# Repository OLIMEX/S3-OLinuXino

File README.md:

# S3-OLinuXino
IP Camera with S3 SOC from Allwinner, PoE 100Mbit, LCD, micro SD, Flash

This board has:
- Allwinner S3 Cortex-A7 running at 1.2Ghz
- 1Gb DDR3 RAM inside S3 SOC up to 1333Mhz
- 100Mb Ethernet interface with PoE option
- NAND/eMMC/SPI Flash on socket
- WiFi / BT module with RTL8723BS 
- Audio In and Out
- UEXT connector
- Configuration EEPROM
- LCD connector for LCD-OLinuXino
- MIPI camera connector
- CSI camera connector
- Dimensions: 60 x 50 mm

# License
- Hardware is with CERN OHL v1.2 license
- Software is with GPLv3 license
- Documentation is with CC BY-SA 4.0 license

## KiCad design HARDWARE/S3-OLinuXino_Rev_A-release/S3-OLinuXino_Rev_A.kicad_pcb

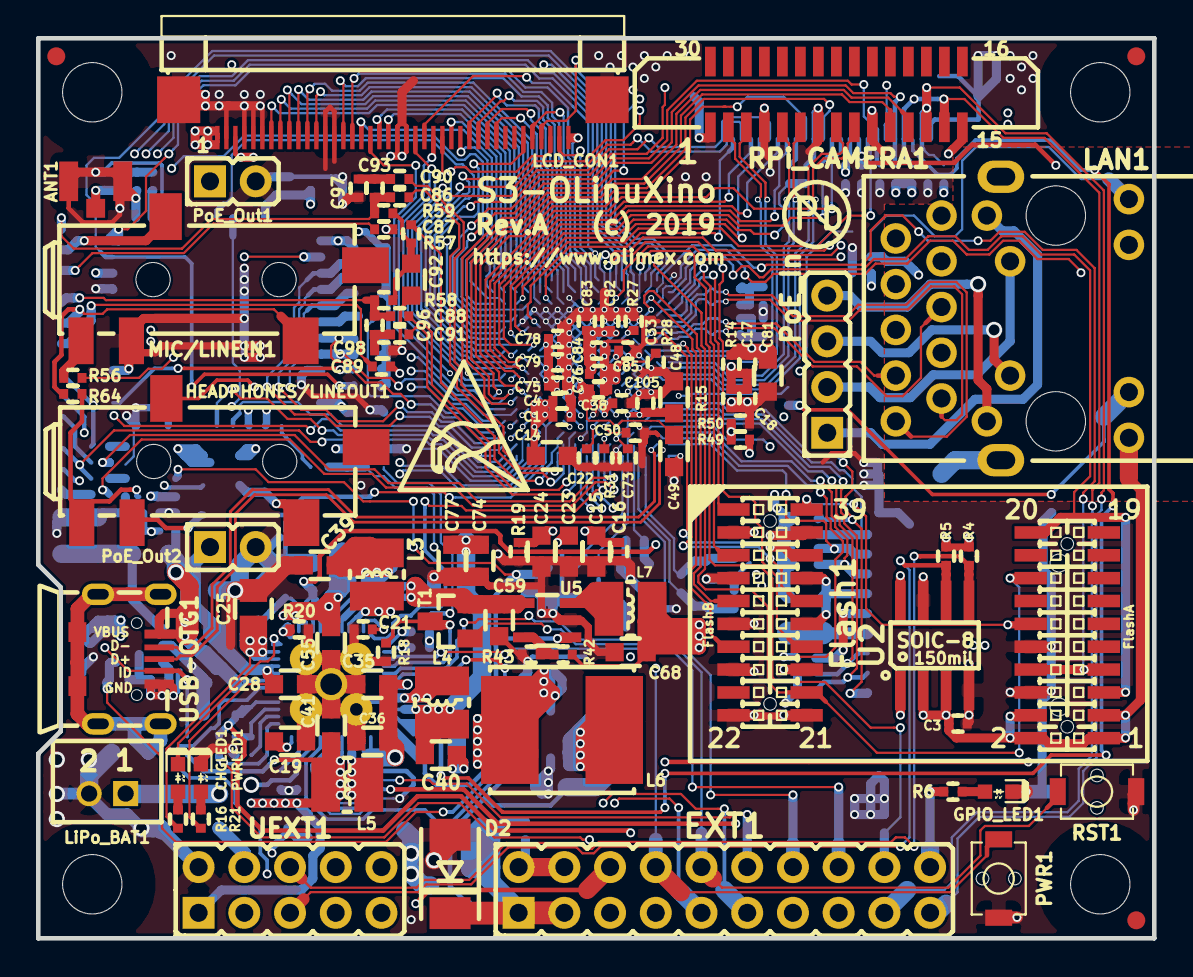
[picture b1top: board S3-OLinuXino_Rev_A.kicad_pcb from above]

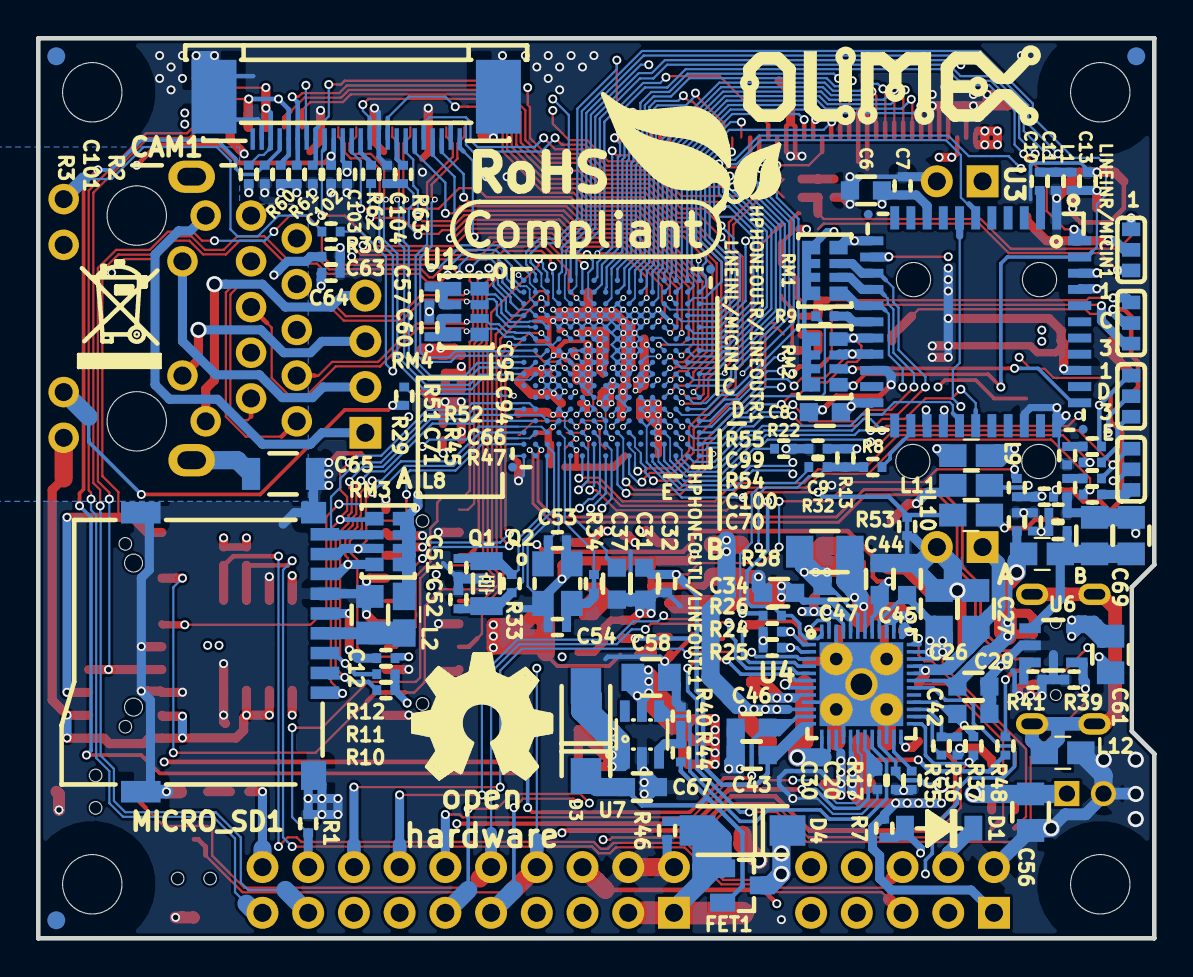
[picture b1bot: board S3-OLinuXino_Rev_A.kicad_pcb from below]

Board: 4 copper layers, 62.0 x 50.0 mm, 233 parts (124 on the bottom side), 224 nets.

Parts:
ANT1: U.FL-R-SMT-1
C1, C3, C4, C7, C9, C16, C17, C18, C20, C22, C33, C38, C57, C60, C63, C64, C66, C71, C73, C75, C76, C78, C79, C82, C83, C84, C85, C86, C87, C88, C89, C90, C91, C94, C95, C99, C100, C101, C102, C103, C105: 100nF/10V/10%/X7R/C0402; C_0402_5MIL_DWS
C6, C8, C14, C15, C29, C31, C34, C35, C36, C39, C40, C41, C55, C59, C67, C68, C74, C77, C81, C92: 10uF/6.3V/20%/X5R/C0603; C_0603_5MIL_DWS
C10: 10pF/50V/5%/COG/C0402; C_0402_5MIL_DWS
C11: 0.8pF/50V/+-0.25pF/COG/C0402; C_0402_5MIL_DWS
C12, C25, C26, C27, C56, C58, C61, C69, C70: 47uF/6.3V/20%/X5R/C0805; C_0805_5MIL_DWS
C13: 1.5pF/50V/+-0.25pF/COG/C0402; C_0402_5MIL_DWS
C19, C47: 2.2uF/6.3V/10%/X5R/C0603; C_0603_5MIL_DWS
C21: 1nF/50V/10%/X7R/C0402; C_0402_5MIL_DWS
C23: NA(10uF/6.3V/20%/X5R/C0603); C_0603_5MIL_DWS
C24, C28, C37, C43, C44, C45, C46, C48, C49: 4.7uF/6.3V/20%/X5R/C0603; C_0603_5MIL_DWS
C30, C32, C50: 100nF/10V/10%/C0402; C_0402_5MIL_DWS
C42: 1uF/10V/20%/X5R/C0603; C_0603_5MIL_DWS
C51, C52: 22pF/50V/5%/COG/C0402; C_0402_5MIL_DWS
C53, C54, C93, C96, C97, C98: 33pF/50V/5%/COG/C0402; C_0402_5MIL_DWS
C65: 1nF/2kV/10%/X7R/C1206; C_1206_5MIL_DWS_ISO
C104: NA(15pF/C0402); C_0402_5MIL_DWS
CAM1: OV2640(FPV-WZB21-24-LF)
CHGLED1: LED/YELLOW/0603; LED_0603_KA
D1: 1N5819(S4SOD-123); SOD-123_1C-2A_KA
D2: SMBJ6.0A; DO214AA_1(K)-2(A)
D3, D4: 1N5822/SS34/SMA; SMA-KA
EXT1: NA(HN2x10); HN2x10
FET1: IRLML6402(SOT-23); SOT23
FID1, FID2, FID3, FID4, FID5, FID6: Fiducial; Fiducial1x3
Flash1: Flash[2x(PA-V16X-2X10-LF)]
GPIO_LED1: LED/Red/0603; LED_0603_KA
HEADPHONES/LINEOUT1: PJ-W47S-05D2-LF; PJ-W47S-05D2-LF_5PIN_V2
HPHONEOUTL/LINEOUTL1: Soldered(1-2);Opened(2-3); SJ_2_SMALL
HPHONEOUTR/LINEOUTR1: Soldered(1-2);Opened(2-3); SJ_2_SMALL
L1: 3.3nH/+-0.1nH/L0402(LQP15MN3N3B02D); L_0402_5MIL_DWS
L2: FB0805/600R/2A; L_0805_5MIL_DWS
L3, L4, L5: 2.2uH/1.5A/72mR/20%/CD32(SPN30302R2MPTE); CD32
L6: 2.2uH/4.5A/28mR/20%/CD75/7.8x7.0x5.0mm(YS75-2R2M); YS75_7X8MM
L7: 2.2uH/1.5A/DCR=72mR/20%/3.00x3.00x1.50mm/CD32(NR3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; CD32
L8, L9, L10, L11, L12: FB0805\600R\2A; L_0805_5MIL_DWS
LAN1: LPJG0926HENL(MagJack_10_100_1000_with_PoE)
LCD_CON1: FPV-WZA21-40-LF
LINEINL/MICIN1: Opened(2-3);Soldered(1-2); SJ_2_SMALL
LINEINR/MICIN1: Opened(2-3);Soldered(1-2); SJ_2_SMALL
LiPo_BAT1: DW02S; LIPO_BAT_VERTICAL_DW02S
Logo-OLimeX_Big: OLIMEX_LOGO_TB
Logo-OSHW: LOGO_OPENHARDWARE_8x8
MH1, MH2, MH3, MH4: Mounting_Hole_NPTH; Mounting_Hole_Drill-3.3mm_Clerance-7mm
MIC/LINEIN1: PJ-W47S-05D2-LF; PJ-W47S-05D2-LF_5PIN_V2
MICRO_SD1: MICRO_SD(TFC-WPAPR-08); TFC-WPAPR-08
PWR1: IT-1185AU2-160G-G-TR; IT1185AU2_V2
PWRLED1: LED\Red\0603; LED_0603_KA
PoE1: [2x(HN1x2)+HN1x4]; PoE[2x(HN1x2)+HN1x4]
Q1: Q32.768kHz/12.5pF/2P/SMD1206; CM7V-T1A(Crystal_Package-1206_3.20x1.50x0.65mm)
Q2: Q24MHZ/20pF/30ppm/4P/3.2x2.5mm; TSX-3.2x2.5mm_GND(3)
R1, R2, R3, R4, R5, R6, R14, R15, R16, R18, R21, R24, R25, R29, R30, R35, R47, R52, R58, R59: 2.2k/R0402; R_0402_5MIL_DWS
R7, R11, R26, R32, R37, R39, R46, R48, R60, R61: 10k/R0402; R_0402_5MIL_DWS
R8, R9, R12, R20, R22, R54, R55, R62, R63: 22R/R0402; R_0402_5MIL_DWS
R10: 100k/R0402; R_0402_5MIL_DWS
R13, R49: NA; R_0402_5MIL_DWS
R17, R19, R51: 200k/1%/R0402; R_0402_5MIL_DWS
R27, R28: 240R/1%/R0402; R_0402_5MIL_DWS
R31: 6.04k/1%/R0402; R_0402_5MIL_DWS
R33: 10M/R0402; R_0402_5MIL_DWS
R34, R53: 0R/R0402(Board_Mounted); R_0402_5MIL_0R(Board_Mounted)
R36: NA(2.2k/R0402); R_0402_5MIL_DWS
R38: 0.03R/1%/R1206; R_1206_5MIL_DWS
R40: 1.1k/1%/R0402; R_0402_5MIL_DWS
R41, R45: 3.9k/1%/R0402; R_0402_5MIL_DWS
R42: 4.99k/1%/R0402; R_0402_5MIL_DWS
R43: 3.32k/1%/R0402; R_0402_5MIL_DWS
R44: 8.25k/1%/R0402; R_0402_5MIL_DWS
R50: 22R; R_0402_5MIL_DWS
R56, R64: NA/R0402; R_0402_5MIL_DWS
R57: 470R/R0402; R_0402_5MIL_DWS
RM1, RM2, RM3: RA1206_(4x0603)_4B8_100k; RA1206_(4X0603)_4B8_xx
RM4: RA1206_(4X0603)_4B8_51R; RA1206_(4X0603)_4B8_xx
RPi_CAMERA1: 1.0mm-pitch_ZIF_SMT-15P; TE_1-1734248-5
RST1: IT-1185AU2-160G-G-TR; IT1185AU2_V2
Sign-Antistatic: LOGO_ANTISTATIC_1
Sign-PbFree: LOGO_PBFREE
Sign-RecycleBin: LOGO_RECYCLEBIN_1
Sign-RoHS: LOGO_ROHS_1
T1: DTA114YKA(SOT-23); SOT23
U1: AllWinner-S3(FBGA-234); FBGA-234(Pitch-0.65mm_Pad-0.3mm_11x11x1.08mm)
U2: AT24C16C-SSHM-T(SOIC-8_150mil); SOIC-8_150mil
U3: RTL8723BS(ComboModule); RL-SM02BD(RTL8723BS)
U4: AXP209(QFN-48); QFN48-6x6mm-OLIMEX_V2
U5: SY8089AAAC(SOT23-5); SOT-23-5
U6: SY6280AAC(SOT23-5); SOT-23-5
U7: MT3608(SOT23-6); SOT23-6
UEXT1: HN2x5
USB-OTG1: MICRO_USB\MISB-SWMM-5B_LF; USB-MICRO_MISB-SWMM-5B_LF

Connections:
+1.1V: C40.2, C49.2, C74.1, C75.1, C76.1, C77.1, C78.1, C79.1, L4.2, U1.G12, U1.H12, U1.J11, U1.J12, U1.K8, U1.K9, U1.K11, U1.L8, U1.M8, U1.N5, U4.10
+1V2: C44.2, C102.2, CAM1.10, U4.41
+2.5V: C30.1, R49.2, U4.19
+2V8: C46.2, C101.2, CAM1.4, U4.11
+3.0VA: C31.2, C32.2, C38.2, C43.2, R51.2, U1.L6, U1.M7, U4.12, U5.1
+3.3V_RTC: C42.2, C50.2, R26.1, R32.1, R37.2, U1.N6, U4.28
+3V3: C1.2, C3.1, C4.2, C6.2, C7.2, C8.2, C9.2, C14.1, C22.1, C41.2, C48.2, C73.1, C103.2, C105.2, CAM1.11, EXT1.7, Flash1.1, Flash1.2, Flash1.3, Flash1.4, L2.1, L5.2, LAN1.15, LAN1.17, LCD_CON1.3, R2.2, R3.2, R4.2, R5.2, R7.2, R10.2, R11.2, R13.2, R24.1, R25.1, R48.2, R60.2, RM1.1.1, RM1.2.1, RM1.3.1, RM1.4.1, RM2.1.1, RM2.2.1, RM2.3.1, RM2.4.1, RM3.1.1, RM3.2.1, RM3.3.1, RM3.4.1, RPi_CAMERA1.15, U1.H11, U1.L11, U1.L12, U1.M4, U1.M5, U1.M11, U1.M12, U1.N7, U1.P5, U1.P12, U2.1, U2.2, U2.3, U2.8, U3.9, U3.22, U4.17, UEXT1.1
+5V: C61.1, D4.1, FET1.3, LCD_CON1.1, U6.5
+5V_EXT: C27.1, C28.1, D2.1, D4.2, EXT1.1, EXT1.3, FET1.1, PoE1.5, PoE1.7, R21.1, R46.2, U4.32, U4.33
+5V_USBOTG: C29.1, C71.1, L8.2, U4.31, USB-OTG1.1
/AP-WAKE-BT: U1.F12, U3.6
/BT-DIS-N: RM2.3.2, U1.C13, U3.34
/BT-PCM-CLK: U1.P14, U3.26
/BT-PCM-DIN: U1.T15, U3.27
/BT-PCM-DOUT: U1.M13, U3.25
/BT-PCM-SYNC: U1.T14, U3.28
/BT-UART-CTS: U1.B8, U3.44
/BT-UART-RX: RM2.4.2, U1.B3, U3.43
/BT-UART-TX: U1.B4, U3.42
/BT-WAKE-AP: U1.N14, U3.7
/CAM-PWDN: CAM1.8, R61.1, U1.D14
/CAM-RST: CAM1.6, R60.1, U1.D15
/CSI-D2: CAM1.24, U1.E12
/CSI-D3: CAM1.23, U1.G15
/CSI-D4: CAM1.19, U1.H13
/CSI-D5: CAM1.21, U1.E13
/CSI-D6: CAM1.22, U1.J13
/CSI-D7: CAM1.20, U1.H14
/CSI-D8: CAM1.18, U1.G14
/CSI-D9: CAM1.16, U1.L13
/CSI-D10: CAM1.14, U1.L16
/CSI-D11: CAM1.12, U1.K13
/CSI-HSYNC: CAM1.9, U1.C14
/CSI-MCLK: R62.2, U1.G13
/CSI-PCLK: C104.1, R63.2, U1.F14
/CSI-VSYNC: CAM1.7, U1.F15
/CTP-INT: LCD_CON1.37, U1.A2
/CTP-RST: LCD_CON1.38, U1.H15
/GPIO_LED: EXT1.20, R6.1, U1.C7
/LCD-PWM: LCD_CON1.36, U1.C8
/LCD_CLK: LCD_CON1.31, U1.A11
/LCD_D2: LCD_CON1.23, U1.K15
/LCD_D3: LCD_CON1.24, U1.C11
/LCD_D4: LCD_CON1.25, U1.J14
/LCD_D5: LCD_CON1.26, U1.J15
/LCD_D6: LCD_CON1.27, U1.B16
/LCD_D7: LCD_CON1.28, U1.C16
/LCD_D10: LCD_CON1.15, U1.B9
/LCD_D11: LCD_CON1.16, U1.A9
/LCD_D12: LCD_CON1.17, U1.C15
/LCD_D13: LCD_CON1.18, U1.L15
/LCD_D14: LCD_CON1.19, U1.A15
/LCD_D15: LCD_CON1.20, U1.B15
/LCD_D18: LCD_CON1.7, U1.B14
/LCD_D19: LCD_CON1.8, U1.A14
/LCD_D20: LCD_CON1.9, U1.B13
/LCD_D21: LCD_CON1.10, U1.A13
/LCD_D22: LCD_CON1.11, U1.B12
/LCD_D23: LCD_CON1.12, U1.C12
/LCD_DE: LCD_CON1.32, U1.B11
/LCD_HSYNC: LCD_CON1.29, U1.C10
/LCD_PWR: LCD_CON1.35, U1.E15
/LCD_VSYNC: LCD_CON1.30, U1.B10
/PB3: EXT1.18, R1.2, U1.C4
/PowerSupply_USB_Audio_Ethernet_Buttons_MiPi-Camera/CHSENSE: C39.2, C47.2, L3.2, R38.2, U4.43
/PowerSupply_USB_Audio_Ethernet_Buttons_MiPi-Camera/CT1: LAN1.11, PoE1.4
/PowerSupply_USB_Audio_Ethernet_Buttons_MiPi-Camera/CT2: LAN1.12, PoE1.3
/PowerSupply_USB_Audio_Ethernet_Buttons_MiPi-Camera/EPHY_LINK_LED: LAN1.16, R29.1
/PowerSupply_USB_Audio_Ethernet_Buttons_MiPi-Camera/EPHY_RX_N: LAN1.6, RM4.4.2, U1.F1
/PowerSupply_USB_Audio_Ethernet_Buttons_MiPi-Camera/EPHY_RX_P: LAN1.3, RM4.3.2, U1.F2
/PowerSupply_USB_Audio_Ethernet_Buttons_MiPi-Camera/EPHY_SPD_LED: LAN1.18, R30.1
/PowerSupply_USB_Audio_Ethernet_Buttons_MiPi-Camera/EPHY_TX_N: LAN1.2, RM4.2.2, U1.E2
/PowerSupply_USB_Audio_Ethernet_Buttons_MiPi-Camera/EPHY_TX_P: LAN1.1, RM4.1.2, U1.E3
/PowerSupply_USB_Audio_Ethernet_Buttons_MiPi-Camera/EXTEN: U4.20, U7.4
/PowerSupply_USB_Audio_Ethernet_Buttons_MiPi-Camera/HPOUTFB: L10.1, R53.2, U1.N11, U1.N12
/PowerSupply_USB_Audio_Ethernet_Buttons_MiPi-Camera/HPOUTL: HPHONEOUTL/LINEOUTL1.1, R54.2, U1.P13
/PowerSupply_USB_Audio_Ethernet_Buttons_MiPi-Camera/HPOUTR: HPHONEOUTR/LINEOUTR1.1, R55.2, U1.N13
/PowerSupply_USB_Audio_Ethernet_Buttons_MiPi-Camera/LINEINL: C89.2, U1.R12
/PowerSupply_USB_Audio_Ethernet_Buttons_MiPi-Camera/LINEINR: C87.2, U1.T12
/PowerSupply_USB_Audio_Ethernet_Buttons_MiPi-Camera/LINEOUTL: C100.1, U1.R6
/PowerSupply_USB_Audio_Ethernet_Buttons_MiPi-Camera/LINEOUTR: C99.1, U1.T6
/PowerSupply_USB_Audio_Ethernet_Buttons_MiPi-Camera/MBIAS: R57.2, U1.P10
/PowerSupply_USB_Audio_Ethernet_Buttons_MiPi-Camera/MCSI_CK+: RPi_CAMERA1.9, U1.J2
/PowerSupply_USB_Audio_Ethernet_Buttons_MiPi-Camera/MCSI_CK-: RPi_CAMERA1.8, U1.J1
/PowerSupply_USB_Audio_Ethernet_Buttons_MiPi-Camera/MCSI_DATA0+: RPi_CAMERA1.3, U1.G3
/PowerSupply_USB_Audio_Ethernet_Buttons_MiPi-Camera/MCSI_DATA0-: RPi_CAMERA1.2, U1.G2
/PowerSupply_USB_Audio_Ethernet_Buttons_MiPi-Camera/MCSI_DATA1+: RPi_CAMERA1.6, U1.H2
/PowerSupply_USB_Audio_Ethernet_Buttons_MiPi-Camera/MCSI_DATA1-: RPi_CAMERA1.5, U1.H1
/PowerSupply_USB_Audio_Ethernet_Buttons_MiPi-Camera/MICIN1_N: C90.2, U1.R10
/PowerSupply_USB_Audio_Ethernet_Buttons_MiPi-Camera/MICIN1_P: C86.2, U1.T10
/PowerSupply_USB_Audio_Ethernet_Buttons_MiPi-Camera/MICIN3_N: C91.2, U1.R9
/PowerSupply_USB_Audio_Ethernet_Buttons_MiPi-Camera/MICIN3_P: C88.2, U1.P9
/PowerSupply_USB_Audio_Ethernet_Buttons_MiPi-Camera/NMI: R26.2, U1.R7, U4.48
/PowerSupply_USB_Audio_Ethernet_Buttons_MiPi-Camera/RESETn: R37.1, U1.P7, U4.25
/PowerSupply_USB_Audio_Ethernet_Buttons_MiPi-Camera/SP1: LAN1.13, PoE1.2
/PowerSupply_USB_Audio_Ethernet_Buttons_MiPi-Camera/SP2: LAN1.14, PoE1.1
/PowerSupply_USB_Audio_Ethernet_Buttons_MiPi-Camera/USB-DRV: R39.2, U4.6, U6.4
/PowerSupply_USB_Audio_Ethernet_Buttons_MiPi-Camera/USB-D_N: U1.R2, USB-OTG1.2
/PowerSupply_USB_Audio_Ethernet_Buttons_MiPi-Camera/USB-D_P: U1.T2, USB-OTG1.3
/PowerSupply_USB_Audio_Ethernet_Buttons_MiPi-Camera/VINT: R35.1, U4.26
/SDC0-CLK: R12.2, U1.P2
/SDC0-CMD: MICRO_SD1.3, R11.1, U1.N2
/SDC0-D0: MICRO_SD1.7, RM3.1.2, U1.P1
/SDC0-D1: MICRO_SD1.8, RM3.2.2, U1.R1
/SDC0-D2: MICRO_SD1.1, RM3.4.2, U1.M2
/SDC0-D3: MICRO_SD1.2, R10.1, U1.N3
/SDC0-DET#: MICRO_SD1.9, RM3.3.2, U1.M1
/SDC2-CLK\SPI0-MISO: Flash1.16, Flash1.23, U1.A3
/SDC2-CMD\SPI0-CLK: Flash1.7, Flash1.8, U1.B2
/SDC2-D0\SPI0-MOSI: Flash1.12, Flash1.39, U1.C2
/SDC2-D1: Flash1.35, U1.F3
/SDC2-D2: Flash1.31, U1.F4
/SDC2-D3: Flash1.27, U1.C1
/SDC2-D4: Flash1.28, U1.C3
/SDC2-D5: Flash1.32, U1.D3
/SDC2-D6: Flash1.36, U1.D2
/SDC2-D7: Flash1.40, U1.D1
/SDC2-RST\SPI0-CS: Flash1.5, Flash1.20, U1.B1
/UART1_RX: D1.2, R7.1, U1.M14
/UART1_TX: U1.M15, UEXT1.3
/WL-PMU-EN: RM1.1.2, U1.E16, U3.12
/WL-SDIO-CLK: R9.2, U1.P16
/WL-SDIO-CMD: RM1.4.2, U1.N15, U3.16
/WL-SDIO-D0: RM2.1.2, U1.P15, U3.18
/WL-SDIO-D1: RM2.2.2, U1.N16, U3.19
/WL-SDIO-D2: RM1.2.2, U1.R15, U3.14
/WL-SDIO-D3: RM1.3.2, U1.R16, U3.15
/WL-WAKE-AP: U1.C5, U3.13
AP-CK32KO: R8.2, R13.1, R32.2, U1.P3
AXP_BACKUP: EXT1.6, U4.30
AXP_GPIO1: EXT1.12, U4.18
AXP_GPIO2: EXT1.14, U4.5
AXP_GPIO3: EXT1.16, U4.3
AXP_PWRON: C21.1, EXT1.8, PWR1.1, U4.47
AXP_RST: EXT1.10, RST1.1, T1.1
CSI-SCK: CAM1.5, EXT1.17, R2.1, RPi_CAMERA1.14, U1.G16
CSI-SDA: CAM1.3, EXT1.19, R3.1, RPi_CAMERA1.13, U1.J16
GND: ANT1.2, C1.1, C3.2, C4.1, C6.1, C7.1, C8.1, C9.1, C11.1, C12.2, C13.1, C14.2, C15.2, C16.2, C18.2, C19.2, C20.2, C21.2, C22.2, C23.2, C24.2, C25.2, C26.2, C27.2, C28.2, C29.2, C30.2, C31.1, C32.1, C33.1, C34.1, C35.1, C36.1, C37.1, C38.1, C39.1, C40.1, C41.1, C42.1, C43.1, C44.1, C45.1, C46.1, C48.1, C49.1, C50.1, C51.1, C52.1, C53.1, C54.1, C55.1, C56.1, C57.1, C58.1, C59.2, C60.1, C61.2, C63.1, C64.1, C65.1, C66.1, C67.1, C68.2, C69.1, C70.1, C71.2, C73.2, C74.2, C75.2, C76.2, C77.2, C78.2, C79.2, C81.2, C82.2, C83.2, C84.2, C85.2, C92.1, C94.1, C95.1, C97.1, C98.2, C101.1, C102.1, C103.1, C104.2, C105.1, CAM1.0, CAM1.2, CAM1.15, D2.2, EXT1.2, EXT1.4, Flash1.6, Flash1.10, Flash1.21, Flash1.22, Flash1.25, Flash1.26, Flash1.29, Flash1.30, Flash1.33, Flash1.34, Flash1.37, Flash1.38, GPIO_LED1.1, L12.1, LCD_CON1.0, LCD_CON1.2, LCD_CON1.4, LCD_CON1.5, LCD_CON1.6, LCD_CON1.13, LCD_CON1.14, LCD_CON1.21, LCD_CON1.22, LiPo_BAT1.2, MIC/LINEIN1.5, MICRO_SD1.6, MICRO_SD1.10, MICRO_SD1.11, MICRO_SD1.12, MICRO_SD1.13, PWR1.2, PWRLED1.1, PoE1.6, PoE1.8, Q2.3, R1.1, R15.2, R17.2, R18.2, R19.2, R20.2, R22.2, R27.1, R28.1, R31.1, R36.1, R39.1, R40.2, R41.1, R43.2, R45.1, R46.1, R50.2, R53.1, R61.2, RPi_CAMERA1.1, RPi_CAMERA1.4, RPi_CAMERA1.7, RPi_CAMERA1.10, RST1.2, U1.A1, U1.A16, U1.C9, U1.D4, U1.D5, U1.D6, U1.D7, U1.D8, U1.D9, U1.D10, U1.D11, U1.D12, U1.E4, U1.E5, U1.E6, U1.E7, U1.E8, U1.E9, U1.E10, U1.E11, U1.E14, U1.F9, U1.F10, U1.F11, U1.G4, U1.G5, U1.G6, U1.G7, U1.G9, U1.G10, U1.G11, U1.H3, U1.H4, U1.H5, U1.H7, U1.H9, U1.H10, U1.J3, U1.J4, U1.J6, U1.J7, U1.J9, U1.J10, U1.K3, U1.K4, U1.K6, U1.K7, U1.K10, U1.K12, U1.L4, U1.L7, U1.L9, U1.L10, U1.M10, U1.N4, U1.N8, U1.P8, U1.R5, U1.T1, U1.T16, U2.4, U2.7, U3.1, U3.20, U3.31, U3.33, U3.36, U3.41, U4.9, U4.16, U4.22, U4.46, U4.49, U5.2, U6.2, U7.2, UEXT1.2, USB-OTG1.5
HP(MIC)-DET: R51.1, R52.2, R56.1, U1.B5
IPS: C20.1, C25.1, C26.1, C34.2, C35.2, C36.2, C45.2, C58.2, C59.1, EXT1.5, L6.1, R16.2, T1.2, U4.7, U4.13, U4.14, U4.21, U4.34, U4.35, U4.40, U4.44, U5.4, U7.5
LRADC0: EXT1.9, U1.T8
LRADC1: EXT1.11, U1.R8
MIPI-CSI-PWDN: RPi_CAMERA1.11, U1.K14
MIPI-CSI-RESET: RPi_CAMERA1.12, U1.L14
unnamed: ANT1.1, C13.2, L1.1
unnamed: C10.1, U3.2
unnamed: C10.2, C11.2, L1.2
unnamed: C12.1, L2.2, MICRO_SD1.4
unnamed: C15.1, C16.1, U1.M9
unnamed: C17.1, C18.1, C33.2, R14.1, R15.1, U1.H6
unnamed: C19.1, U4.24
unnamed: C23.1, U1.N9
unnamed: C24.1, R19.1, U1.N10
unnamed: C37.2, U1.T5
unnamed: C51.2, Q1.1, R33.1, U1.T3
unnamed: C52.2, Q1.2, R33.2, U1.R3
unnamed: C53.2, Q2.1, U1.R4
unnamed: C54.2, Q2.2, R34.2
unnamed: C57.2, RM4.1.1, RM4.2.1
unnamed: C60.2, RM4.3.1, RM4.4.1
unnamed: C63.2, LAN1.4
unnamed: C64.2, LAN1.5
unnamed: C65.2, LAN1.0
unnamed: C67.2, D3.1, FET1.2, R44.1
unnamed: C69.2, C70.2, L8.1, R47.2, U6.1
unnamed: C86.1, C93.1, LINEINR/MICIN1.1, R59.1
unnamed: C87.1, LINEINR/MICIN1.3
unnamed: C88.1, C96.1, LINEINL/MICIN1.1, R58.1
unnamed: C89.1, LINEINL/MICIN1.3
unnamed: C90.1, C93.2, C97.2
unnamed: C91.1, C96.2, C98.1
unnamed: C92.2, R57.1, R58.2, R59.2
unnamed: C94.2, R54.1
unnamed: C95.2, R55.1
unnamed: C99.2, HPHONEOUTR/LINEOUTR1.3
unnamed: C100.2, HPHONEOUTL/LINEOUTL1.3
unnamed: CAM1.13, R62.1
unnamed: CAM1.17, R63.1
unnamed: CHGLED1.1, U4.36
unnamed: CHGLED1.2, R16.1
unnamed: D1.1, UEXT1.4
unnamed: D3.2, L6.2, U7.1
unnamed: GPIO_LED1.2, R6.2
unnamed: HEADPHONES/LINEOUT1.1, R52.1, R64.1
unnamed: HEADPHONES/LINEOUT1.2, L11.2
unnamed: HEADPHONES/LINEOUT1.3, L9.2
unnamed: HEADPHONES/LINEOUT1.5, L10.2
unnamed: HPHONEOUTL/LINEOUTL1.2, L11.1
unnamed: HPHONEOUTR/LINEOUTR1.2, L9.1
unnamed: L3.1, U4.45
unnamed: L4.1, U4.8
unnamed: L5.1, U4.15
unnamed: L7.1, U5.3
unnamed: L12.2, USB-OTG1.0
unnamed: LINEINL/MICIN1.2, MIC/LINEIN1.2, R64.2
unnamed: LINEINR/MICIN1.2, MIC/LINEIN1.3
unnamed: MIC/LINEIN1.1, R56.2
unnamed: MICRO_SD1.5, R12.1
unnamed: PWRLED1.2, R21.2
unnamed: R8.1, U3.24
unnamed: R9.1, U3.17
unnamed: R17.1, U4.23
unnamed: R18.1, T1.3, U4.4
unnamed: R20.1, U4.37
unnamed: R22.1, U1.R13
unnamed: R27.2, U1.F5
unnamed: R28.2, U1.J5
unnamed: R29.2, U1.K5
unnamed: R30.2, U1.L5
unnamed: R31.2, U1.P6
unnamed: R34.1, U1.P4
unnamed: R35.2, R36.2, U4.27
unnamed: R40.1, R44.2, U7.3
unnamed: R41.2, U6.3
unnamed: R42.1, R43.1, U5.5
unnamed: R49.1, R50.1, U1.M6
PB6\TWI0-SCK: EXT1.13, LCD_CON1.39, R25.2, U1.A7, U4.2
PB7\TWI0-SDA: EXT1.15, LCD_CON1.40, R24.2, U1.B7, U4.1
PB8\TWI1-SCK: R5.1, U1.B6, U2.6, UEXT1.5
PB9\TWI1-SDA: R4.1, U1.C6, U2.5, UEXT1.6
USB-ID: R48.1, U1.R14, USB-OTG1.4
USB-VBUSDET: C66.2, R45.2, R47.1, U1.A5
VBAT: C47.1, C55.2, C56.2, LiPo_BAT1.1, R38.1, U4.38, U4.39, U4.42
VCC-DDR: C17.2, C68.1, C81.1, C82.1, C83.1, C84.1, C85.1, L7.2, R14.2, R42.2, U1.F6, U1.F7, U1.F8, U1.G8, U1.H8, U1.J8

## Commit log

2019-10-25 initial upload schematic and pcb placements
2020-04-24 Release
    revision A release design

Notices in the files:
HARDWARE/S3-OLinuXino_Rev_A-release/S3-OLinuXino_Rev_A.kicad_pcb:
(c) 2019
